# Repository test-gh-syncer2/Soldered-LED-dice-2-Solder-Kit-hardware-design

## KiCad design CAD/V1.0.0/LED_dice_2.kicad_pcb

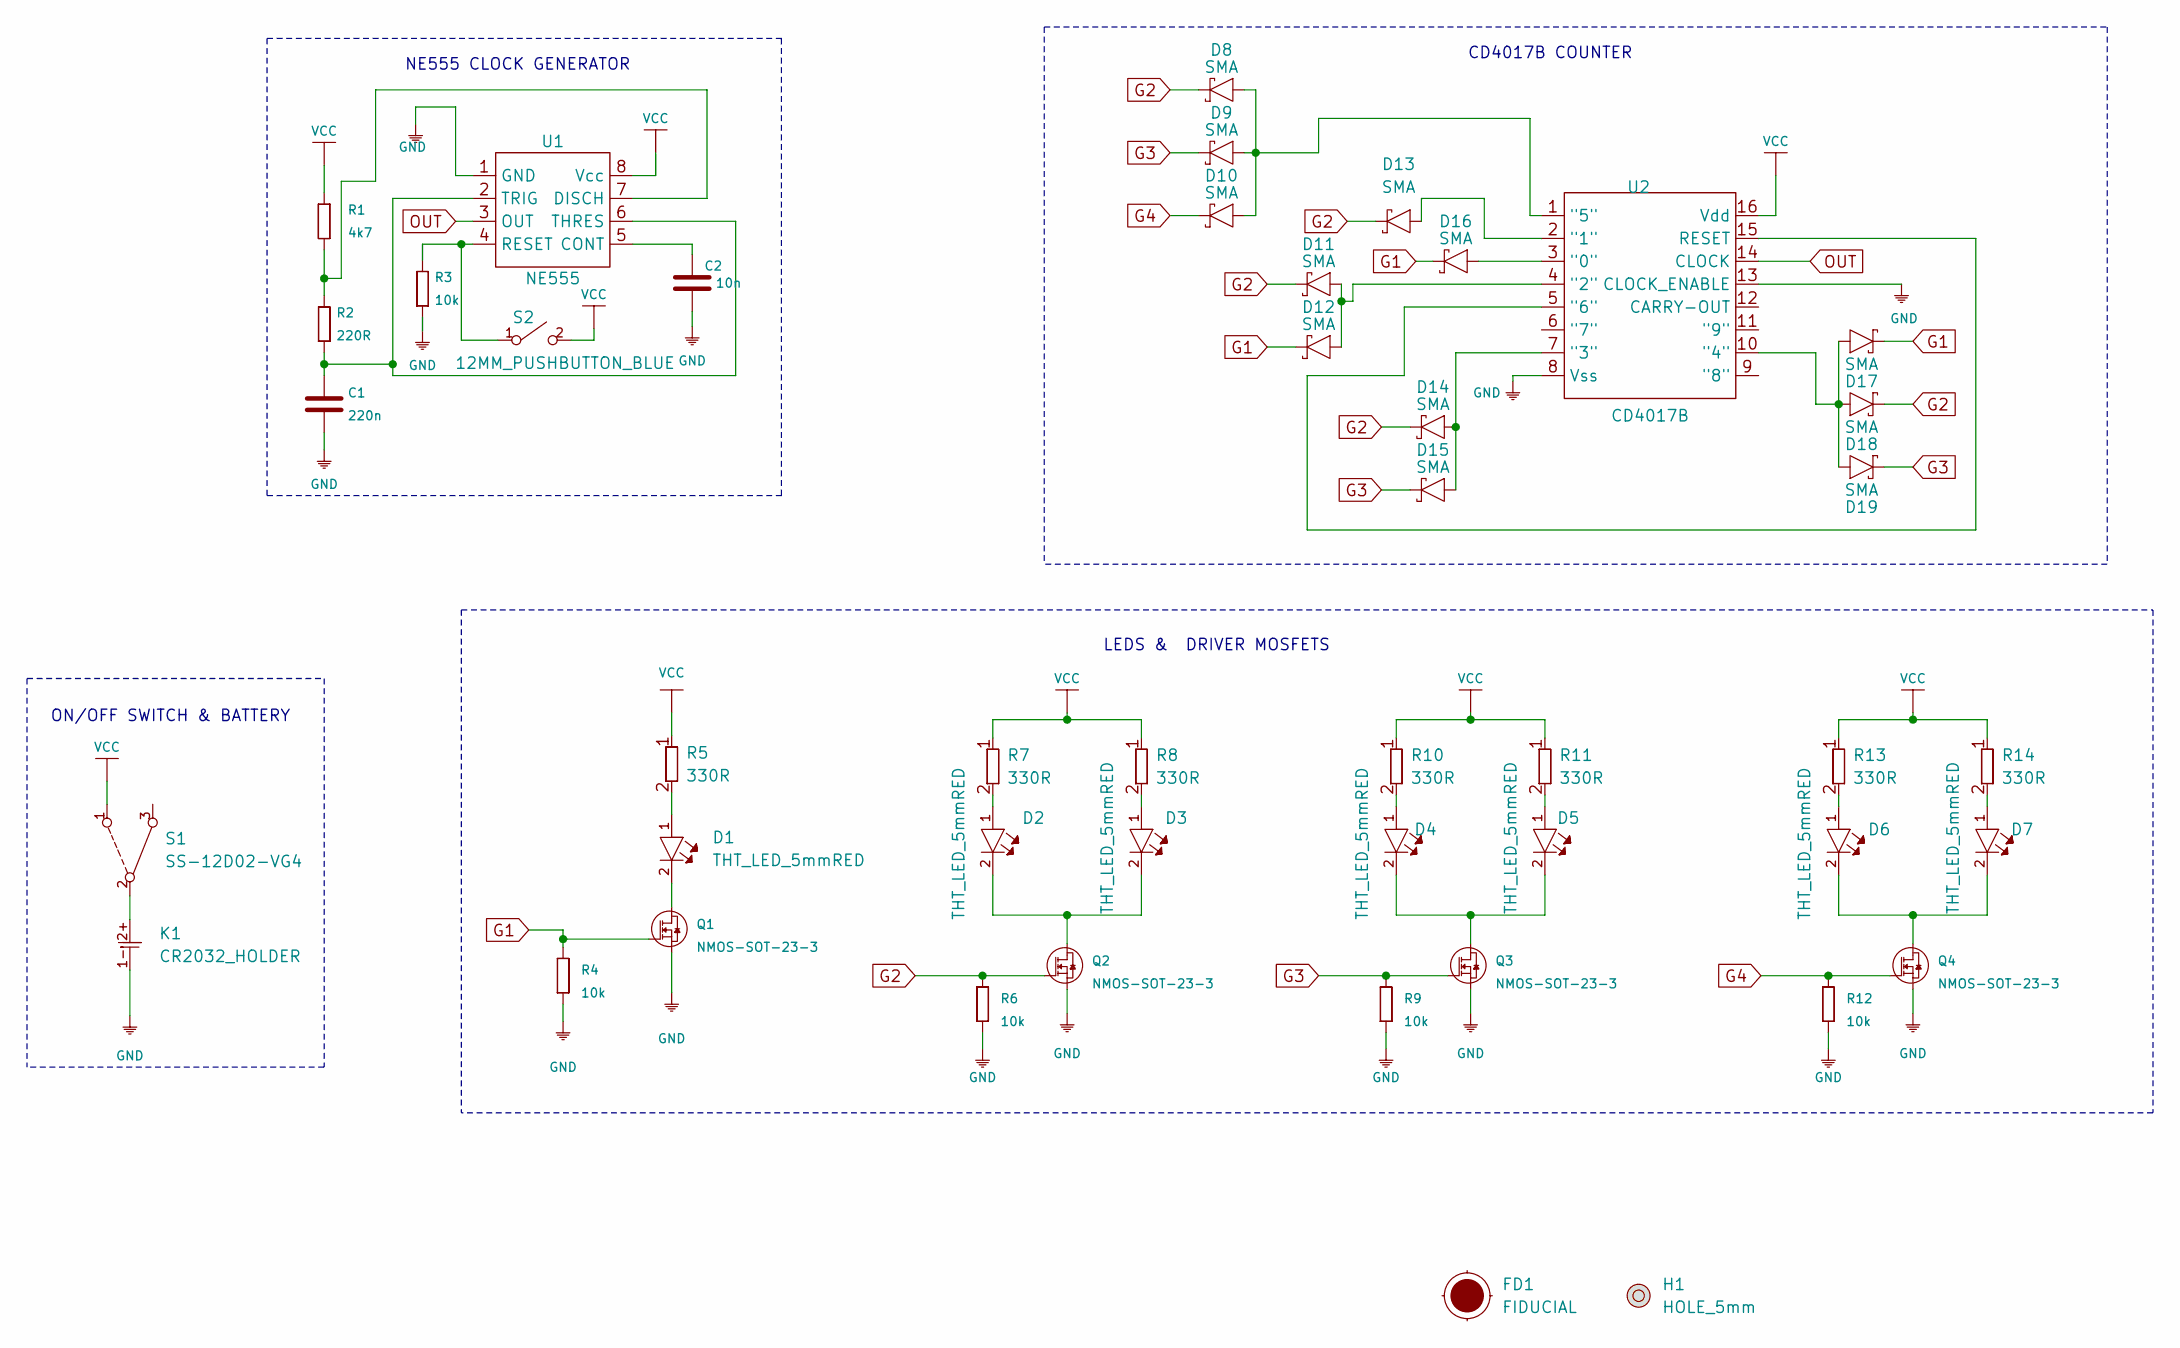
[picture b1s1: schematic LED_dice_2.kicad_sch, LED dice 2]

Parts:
C1: 220n; 0603C
C2: 10n; 0603C
D1, D2, D3, D4, D5, D6, D7: THT_LED_5mmRED; THT LED 5mm RED
D8, D9, D10, D11, D12, D13, D14, D15, D16, D17, D18, D19: SMA; SMA_DIODE
FD1: FIDUCIAL; FIDUCIAL_23
H1: HOLE_5mm
K1: CR2032_HOLDER; CR2034_HOLDER
Q1, Q2, Q3, Q4: NMOS-SOT-23-3; SOT-23-3
R1: 4k7; 0603R
R2: 220R; 0603R
R3, R4, R6, R9, R12: 10k; 0603R
R5, R7, R8, R10, R11, R13, R14: 330R; THT OTPORNIK
S1: SS-12D02-VG4
S2: 12MM_PUSHBUTTON_BLUE; PUSH BUTTON 12MM BLUE
U1: NE555; DIP8
U2: CD4017B; SOP-16

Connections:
G1: D12.2 (C), D16.2 (C), D17.2 (C), Q1.1 (G), R4.2
G2: D8.2 (C), D11.2 (C), D13.2 (C), D14.2 (C), D18.2 (C), Q2.1 (G), R6.2
G3: D9.2 (C), D15.2 (C), D19.2 (C), Q3.1 (G), R9.2
G4: D10.2 (C), Q4.1 (G), R12.2
GND: C1.1, C2.1, K1.1-, Q1.2 (S), Q2.2 (S), Q3.2 (S), Q4.2 (S), R3.1, R4.1, R6.1, R9.1, R12.1, U1.1 (GND), U2.8 (Vss), U2.13 (CLOCK_ENABLE)
unnamed: C1.2, R2.1, U1.2 (TRIG), U1.6 (THRES)
unnamed: C2.2, U1.5 (CONT)
unnamed: D1.1, R5.2
unnamed: D1.2, Q1.3 (D)
unnamed: D2.1, R7.2
unnamed: D2.2, D3.2, Q2.3 (D)
unnamed: D3.1, R8.2
unnamed: D4.1, R10.2
unnamed: D5.1, R11.2
unnamed: D4.2, D5.2, Q3.3 (D)
unnamed: D6.1, R13.2
unnamed: D6.2, D7.2, Q4.3 (D)
unnamed: D7.1, R14.2
unnamed: K1.2+, S1.2
unnamed: R1.2, R2.2, U1.7 (DISCH)
unnamed: R3.2, S2.1, U1.4 (RESET)
unnamed: D8.1 (A), D9.1 (A), D10.1 (A), U2.1 ("5")
unnamed: D13.1 (A), U2.2 ("1")
unnamed: D16.1 (A), U2.3 ("0")
unnamed: D11.1 (A), D12.1 (A), U2.4 ("2")
unnamed: D14.1 (A), D15.1 (A), U2.7 ("3")
unnamed: D17.1 (A), D18.1 (A), D19.1 (A), U2.10 ("4")
unnamed: U2.5 ("6"), U2.15 (RESET)
OUT: U1.3 (OUT), U2.14 (CLOCK)
VCC: R1.1, R5.1, R7.1, R8.1, R10.1, R11.1, R13.1, R14.1, S1.1, S2.2, U1.8 (Vcc), U2.16 (Vdd)

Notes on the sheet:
ON/OFF SWITCH & BATTERY
NE555 CLOCK GENERATOR
LEDS & DRIVER MOSFETS
CD4017B COUNTER

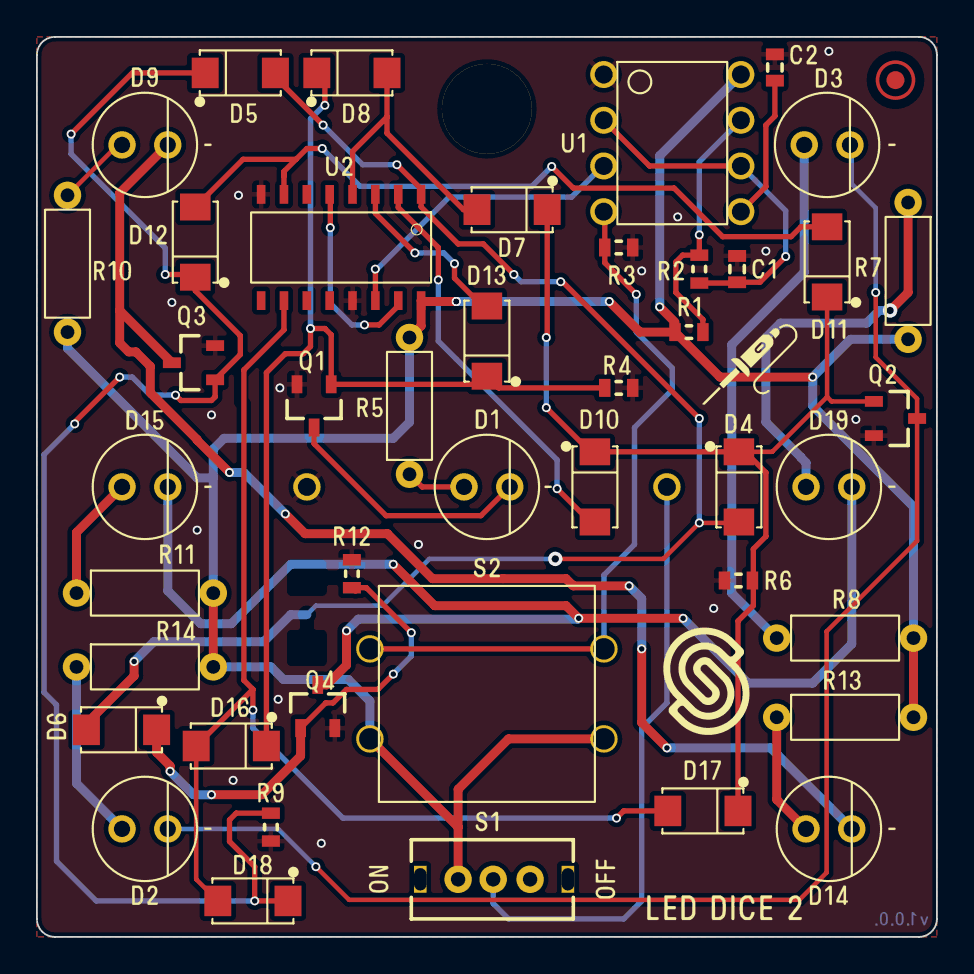
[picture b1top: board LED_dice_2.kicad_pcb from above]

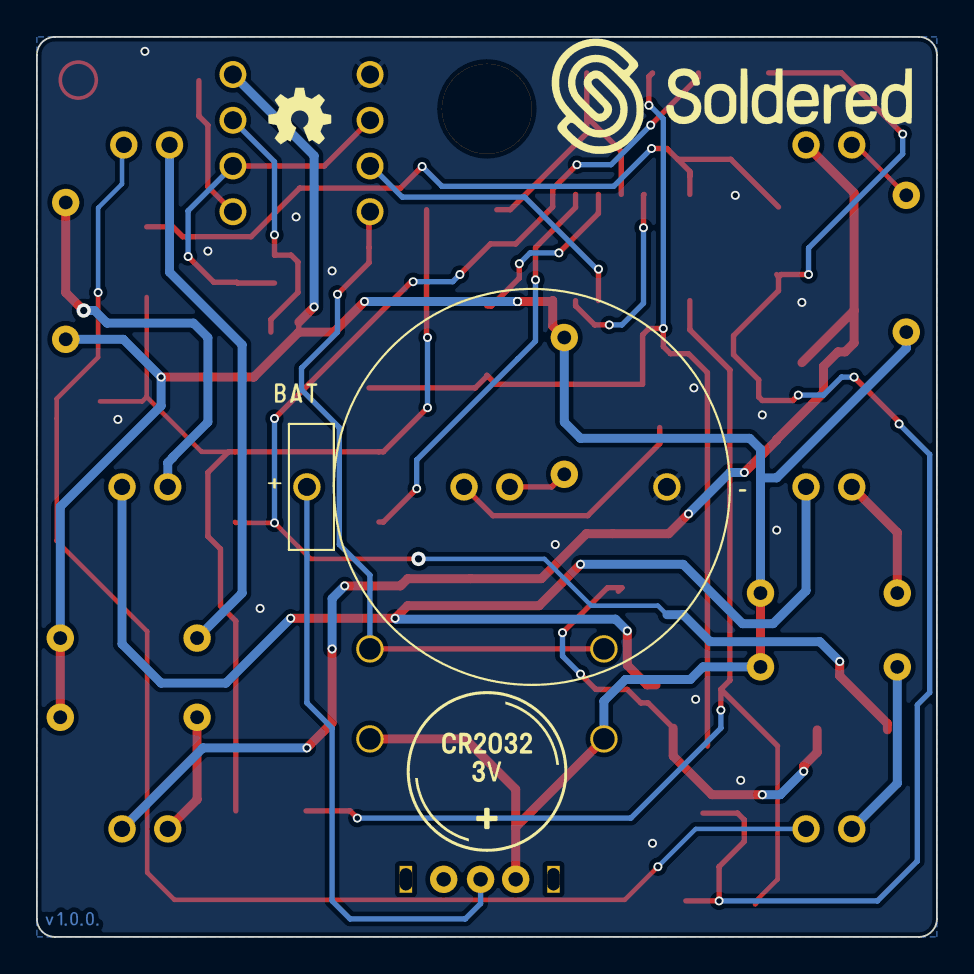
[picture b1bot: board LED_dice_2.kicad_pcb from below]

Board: 2 copper layers, 50.0 x 50.0 mm, 47 parts (2 on the bottom side), 30 nets.

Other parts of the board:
Ref**: Val**; Version1.0.0.

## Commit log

2021-09-23 Syncing to git
2021-09-23 Updating open source files.
